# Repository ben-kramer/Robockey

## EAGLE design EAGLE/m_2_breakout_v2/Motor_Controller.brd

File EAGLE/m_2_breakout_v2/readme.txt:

Notes on PCB etching:
1. Make sure you are printing a mirror of the board in EAGLE.
2. print consecutive boards on different parts of the page to save transparencies
	a. Do a test print: put a sharpie mark on the top-side, upper left corner of the page to see which way the printer takes paper
	b. Alternatively, group everything on 1 page first! Prepare singles (pages with just 1
	   design per) and full pages. Print the full page first, and reprint any extras. Make sure
	   singles are in different spots.

issues:
1. M2 needs a jump to ground
2. where does mRF go?

etching method
0. designing
	a. for single-layer boards, design circuit using the bottom layer. Wires are on the sides
	   opposite to the things you are mounting.
1. printing
	a. do a test print to make sure you know what direction the printer prints
	b. from EAGLE, make a pdf (or JPEG?) of the circuit that is BLACK and NOTNOTNOT MIRRORED
		i. look into using JPEGs so multiple pictures can be merged into 1 sheet
	c. take a transparency and mark it with a k or other non-symmetrical letter on the top left
	d. print out the circuits
		i. top and bottom layers
		ii. pad layer
		iii. hole layer
	e. fill in any holes with a fine-tip sharpie
	f. cut out circuits using scissors or xacto. Place circuit on top of board and cut (xacto works nicely for this). Mark anything else (like holes) that is too thin with a sharpie
2. Etching step 1 - photodevelopment
	a. clean transparency first with a duster can and water thorougly.
	b. minimizing fingerprints, wet a lintless towel/cloth with water and gently
	   rub it across the top of the circuit transparency. Make sure to spread the
	   water evenly.
	c. turn off lights, turn on red lights
	d. unpeel protective layer from copper and stick the transparency to the board using the water on the board. Compress the two to ensure they stick together.
	d. Place the board under glass and turn the LED light on for 10 minutes.
	e. Remove board from LED light, turning it off, and place in etching solution. With glove,
	   wiggle board around. This should take no more than 1.5 minutes. If it takes longer, add
	   more positive developer. Towards the end you might have to take one side of the board out
	   and swish around only a fraction of it because the photoresist doesn't develop perfectly
	   evenly.
	f. wash board under cold water
	g. dry board
	h. fill in errors with sharpie
3. Etching step 2 - etching
	a. place board in cupric acid. Ensure cupric acid is a nice green. If it's yellow or brown,
	   add more H202.
	b. swish with the large end of a funnel until board etches.
	c. Note: if etching is still slow after adding H202, add some HCl
	d. rinse board in cold water
	e. rinse board with acetone.
		i. put a little acetone on top of the board, swish it around, and remove it with a sponge.
	f. check for errors
		i. label each error found on the board. Put identifying marks below or to the right of the area, unless doing so is impossible.

todo:

update pinmap

1. add out for breakbeam led
2. add switch bank
3. add bicolor led spot
4. switch motor signal connectors

add enable pins for bridges

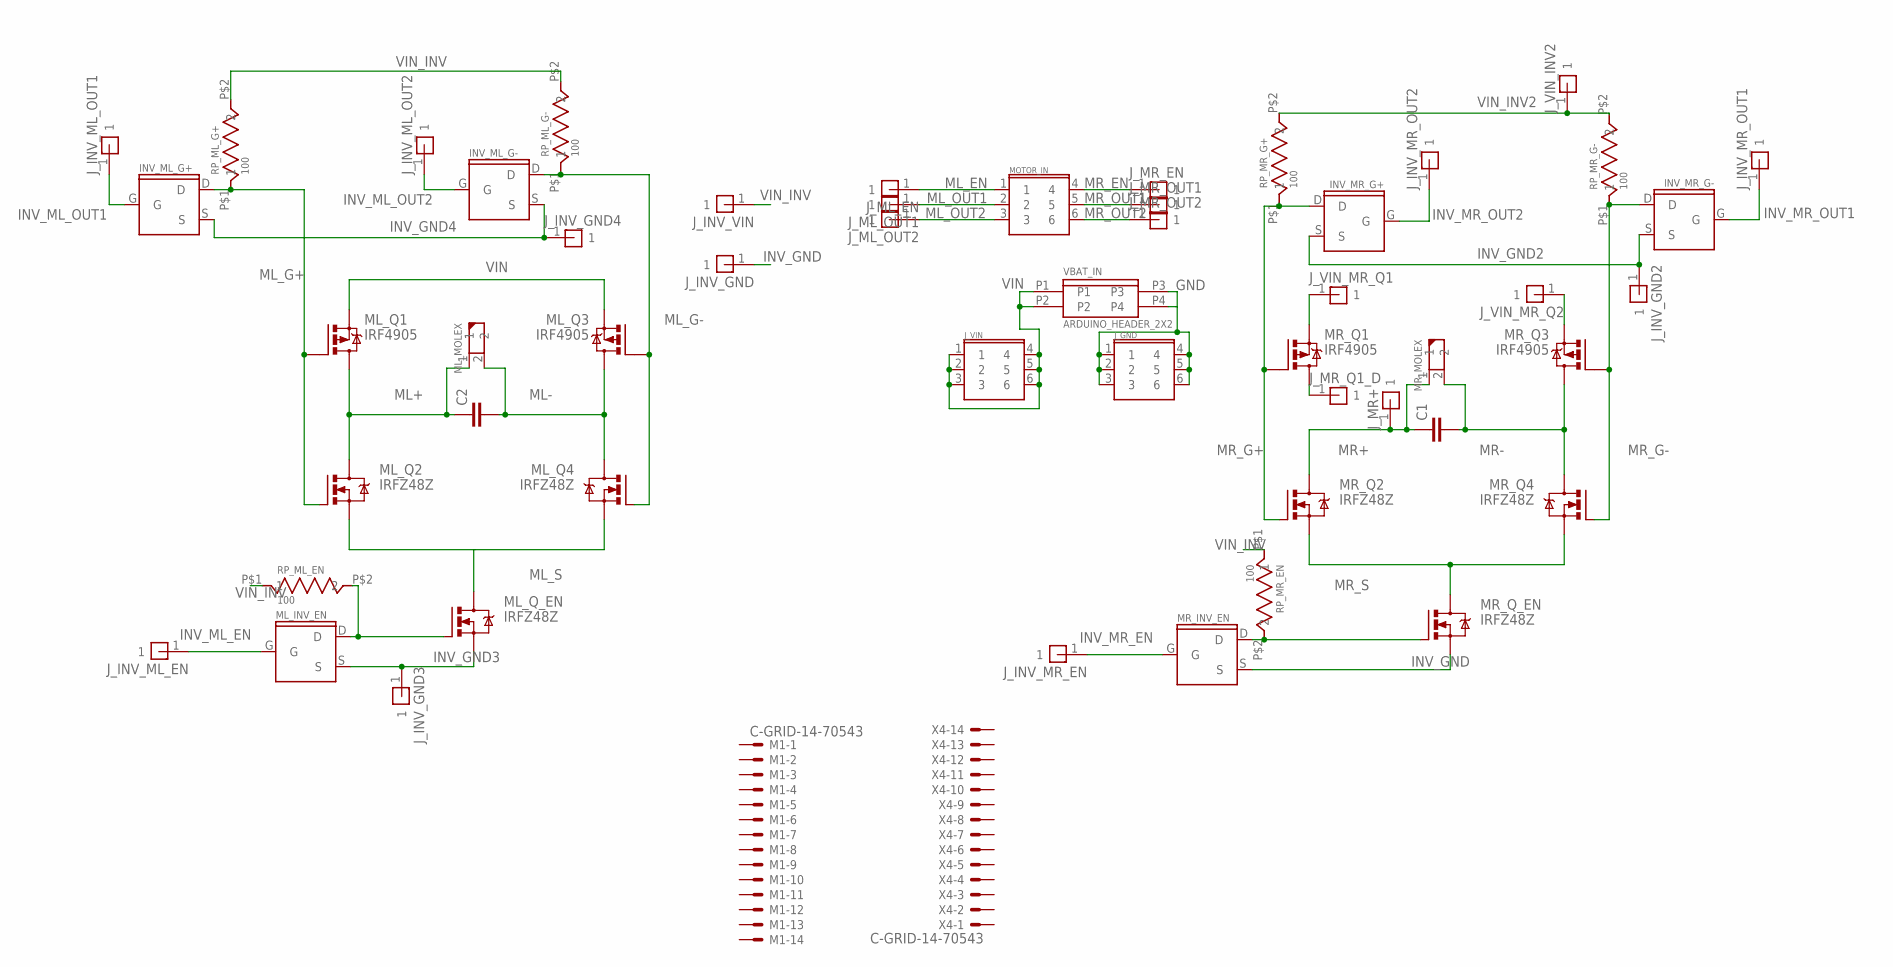
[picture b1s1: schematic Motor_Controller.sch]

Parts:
C1, C2: C5/3; C5B3
INV_ML_G+: 2N7000; TO-92
INV_ML_G-: 2N7000; TO-92
INV_MR_G+: 2N7000; TO-92
INV_MR_G-: 2N7000; TO-92
J_GND: ARDUINO_HEADER_3X2
J_INV_GND, J_INV_GND2, J_INV_GND3, J_INV_GND4: ARDUINO_HEADER_1X1_OCTAGON
J_INV_ML_EN: ARDUINO_HEADER_1X1_OCTAGON
J_INV_ML_OUT1, J_INV_ML_OUT2: ARDUINO_HEADER_1X1_OCTAGON
J_INV_MR_EN: ARDUINO_HEADER_1X1_OCTAGON
J_INV_MR_OUT1, J_INV_MR_OUT2: ARDUINO_HEADER_1X1_OCTAGON
J_INV_VIN: ARDUINO_HEADER_1X1_OCTAGON
J_ML_EN: ARDUINO_HEADER_1X1_OCTAGON
J_ML_OUT1, J_ML_OUT2: ARDUINO_HEADER_1X1_OCTAGON
J_MR+: ARDUINO_HEADER_1X1_OCTAGON
J_MR_EN: ARDUINO_HEADER_1X1_OCTAGON
J_MR_OUT1, J_MR_OUT2: ARDUINO_HEADER_1X1_OCTAGON
J_MR_Q1_D: ARDUINO_HEADER_1X1_OCTAGON
J_VIN: ARDUINO_HEADER_3X2
J_VIN_INV2: ARDUINO_HEADER_1X1_OCTAGON
J_VIN_MR_Q1, J_VIN_MR_Q2: ARDUINO_HEADER_1X1_OCTAGON
M1: C-GRID-14-70543; 70543-14
ML_INV_EN: 2N7000; TO-92
ML_MOLEX: MOLEX_2_PIN
ML_Q1, ML_Q3: IRF4905; TO220BH
ML_Q2, ML_Q4: IRFZ48Z; TO220BH
ML_Q_EN: IRFZ48Z; TO220BH
MOTOR_IN: ARDUINO_HEADER_3X2
MR_INV_EN: 2N7000; TO-92
MR_MOLEX: MOLEX_2_PIN
MR_Q1, MR_Q3: IRF4905; TO220BH
MR_Q2, MR_Q4: IRFZ48Z; TO220BH
MR_Q_EN: IRFZ48Z; TO220BH
RP_ML_EN: 100; RESISTOR_THROUGH_8MM
RP_ML_G+: 100; RESISTOR_THROUGH_8MM
RP_ML_G-: 100; RESISTOR_THROUGH_8MM
RP_MR_EN: 100; RESISTOR_THROUGH_8MM
RP_MR_G+: 100; RESISTOR_THROUGH_8MM
RP_MR_G-: 100; RESISTOR_THROUGH_8MM
VBAT_IN: ARDUINO_HEADER_2X2
X4: C-GRID-14-70543; 70543-14

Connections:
GND: J_GND.1, J_GND.2, J_GND.3, J_GND.4, J_GND.5, J_GND.6, VBAT_IN.P3, VBAT_IN.P4
INV_GND: J_INV_GND.1, MR_INV_EN.S, MR_Q_EN.S
INV_GND2: INV_MR_G+.S, INV_MR_G-.S, J_INV_GND2.1
INV_GND3: J_INV_GND3.1, ML_INV_EN.S, ML_Q_EN.S
INV_GND4: INV_ML_G+.S, INV_ML_G-.S, J_INV_GND4.1
INV_ML_EN: J_INV_ML_EN.1, ML_INV_EN.G
INV_ML_OUT1: INV_ML_G+.G, J_INV_ML_OUT1.1
INV_ML_OUT2: INV_ML_G-.G, J_INV_ML_OUT2.1
INV_MR_EN: J_INV_MR_EN.1, MR_INV_EN.G
INV_MR_OUT1: INV_MR_G-.G, J_INV_MR_OUT1.1
INV_MR_OUT2: INV_MR_G+.G, J_INV_MR_OUT2.1
ML+: C2.1, ML_MOLEX.1, ML_Q1.D, ML_Q2.D
ML-: C2.2, ML_MOLEX.2, ML_Q3.D, ML_Q4.D
ML_EN: J_ML_EN.1, MOTOR_IN.1
ML_G+: INV_ML_G+.D, ML_Q1.G, ML_Q2.G, RP_ML_G+.P$1 (1)
ML_G-: INV_ML_G-.D, ML_Q3.G, ML_Q4.G, RP_ML_G-.P$1 (1)
ML_OUT1: J_ML_OUT1.1, MOTOR_IN.2
ML_OUT2: J_ML_OUT2.1, MOTOR_IN.3
ML_S: ML_Q2.S, ML_Q4.S, ML_Q_EN.D
MR+: C1.1, J_MR+.1, MR_MOLEX.1, MR_Q2.D
MR-: C1.2, MR_MOLEX.2, MR_Q3.D, MR_Q4.D
MR_EN: J_MR_EN.1, MOTOR_IN.4
MR_G+: INV_MR_G+.D, MR_Q1.G, MR_Q2.G, RP_MR_G+.P$1 (1)
MR_G-: INV_MR_G-.D, MR_Q3.G, MR_Q4.G, RP_MR_G-.P$1 (1)
MR_OUT1: J_MR_OUT1.1, MOTOR_IN.5
MR_OUT2: J_MR_OUT2.1, MOTOR_IN.6
MR_Q1_D: J_MR_Q1_D.1, MR_Q1.D
MR_S: MR_Q2.S, MR_Q4.S, MR_Q_EN.D
unnamed: MR_INV_EN.D, MR_Q_EN.G, RP_MR_EN.P$2 (2)
unnamed: ML_INV_EN.D, ML_Q_EN.G, RP_ML_EN.P$2 (2)
unnamed: J_VIN_MR_Q1.1, MR_Q1.S
unnamed: J_VIN_MR_Q2.1, MR_Q3.S
VIN: J_VIN.1, J_VIN.2, J_VIN.3, J_VIN.4, J_VIN.5, J_VIN.6, ML_Q1.S, ML_Q3.S, VBAT_IN.P1, VBAT_IN.P2
VIN_INV: J_INV_VIN.1, RP_ML_EN.P$1 (1), RP_ML_G+.P$2 (2), RP_ML_G-.P$2 (2), RP_MR_EN.P$1 (1)
VIN_INV2: J_VIN_INV2.1, RP_MR_G+.P$2 (2), RP_MR_G-.P$2 (2)

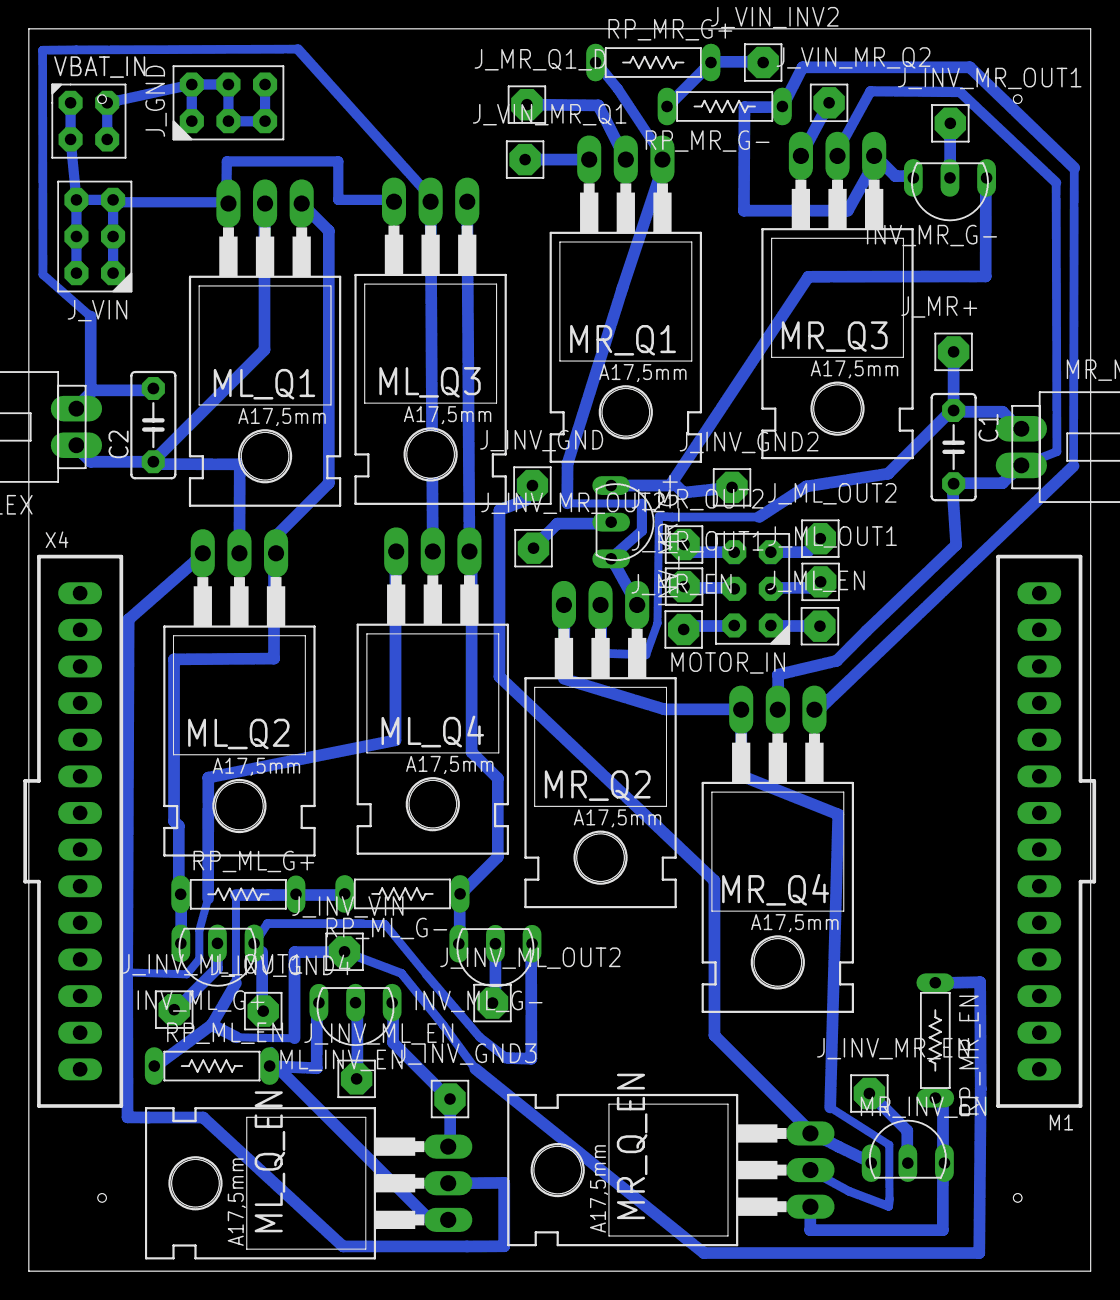
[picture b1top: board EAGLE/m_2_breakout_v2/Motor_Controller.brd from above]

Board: 2 copper layers, 73.6 x 86.2 mm, 54 parts (0 on the bottom side), 35 nets.

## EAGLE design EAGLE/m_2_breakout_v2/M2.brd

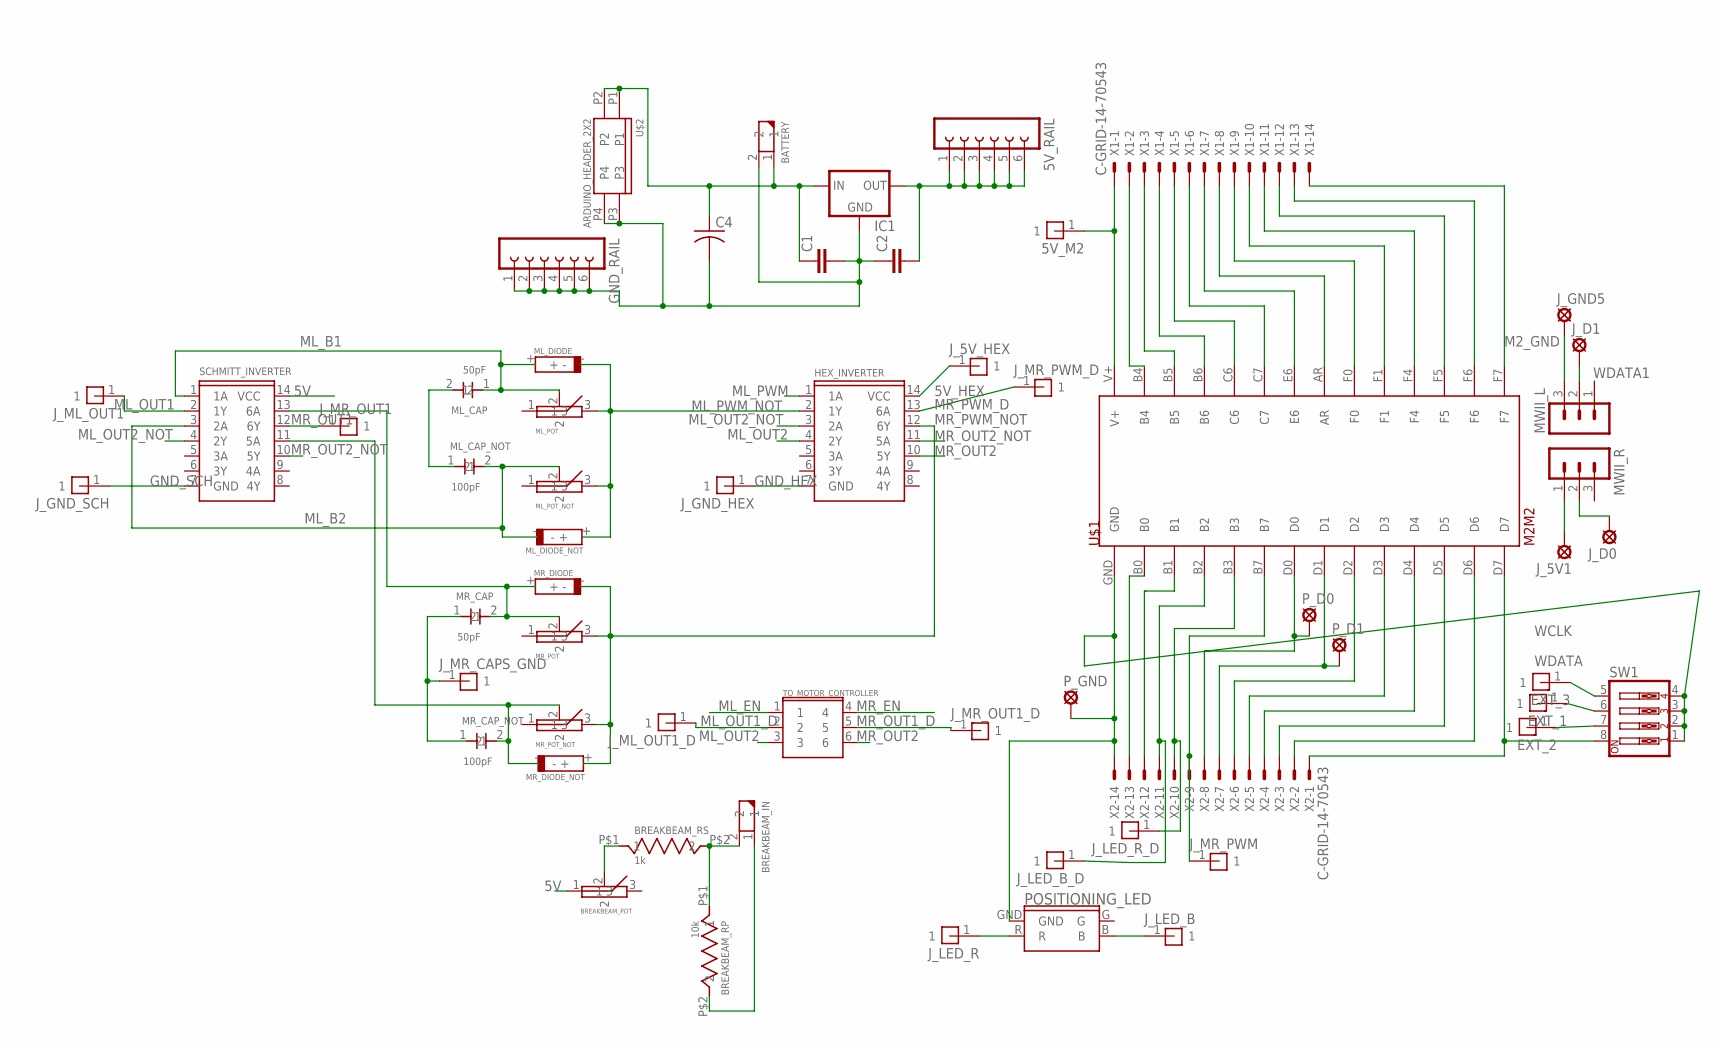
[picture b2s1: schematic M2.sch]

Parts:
5V_M2: ARDUINO_HEADER_1X1_OCTAGON
5V_RAIL: FE06-1; FE06
BATTERY: MOLEX_2_PIN
BREAKBEAM_IN: MOLEX_2_PIN
BREAKBEAM_POT: POTENTIOMETER_1
BREAKBEAM_RP: 10k; RESISTOR_THROUGH_8MM
BREAKBEAM_RS: 1k; RESISTOR_THROUGH_8MM
C1, C2: C2,5-3; C2.5-3
C4: C-US050-025X075; C050-025X075
EXT_1, EXT_2, EXT_3: ARDUINO_HEADER_1X1_OCTAGON
GND_RAIL: FE06-1; FE06
HEX_INVERTER: SN74HC04N_HEX_INVERTER; DIP14
IC1: 78MXXS
J_5V1: LSP10
J_5V_HEX: ARDUINO_HEADER_1X1_OCTAGON
J_D0, J_D1: LSP10
J_GND5: LSP10
J_GND_HEX: ARDUINO_HEADER_1X1_OCTAGON
J_GND_SCH: ARDUINO_HEADER_1X1_OCTAGON
J_LED_B: ARDUINO_HEADER_1X1_OCTAGON
J_LED_B_D: ARDUINO_HEADER_1X1_OCTAGON
J_LED_R: ARDUINO_HEADER_1X1_OCTAGON
J_LED_R_D: ARDUINO_HEADER_1X1_OCTAGON
J_ML_OUT1, J_ML_OUT1_D: ARDUINO_HEADER_1X1_OCTAGON
J_MR_CAPS_GND: ARDUINO_HEADER_1X1_OCTAGON
J_MR_OUT1, J_MR_OUT1_D: ARDUINO_HEADER_1X1_OCTAGON
J_MR_PWM: ARDUINO_HEADER_1X1_OCTAGON
J_MR_PWM_D: ARDUINO_HEADER_1X1_OCTAGON
ML_CAP: 50pF; CERAMIC_CAPACITOR
ML_CAP_NOT: 100pF; CERAMIC_CAPACITOR
ML_DIODE: 1N914B
ML_DIODE_NOT: 1N914B
ML_POT: POTENTIOMETER_1
ML_POT_NOT: POTENTIOMETER_1
MR_CAP: 50pF; CERAMIC_CAPACITOR
MR_CAP_NOT: 100pF; CERAMIC_CAPACITOR
MR_DIODE: 1N914B
MR_DIODE_NOT: 1N914B
MR_POT: POTENTIOMETER_1
MR_POT_NOT: POTENTIOMETER_1
MWII_L: MA03-1
MWII_R: MA03-1
POSITIONING_LED: RGB_LED; RBG_LED
P_D0, P_D1: LSP10
P_GND: LSP10
SCHMITT_INVERTER: SN74HC14N_SCHMITT_INVERTER; DIP14
SW1: SW_DIP-4; EDG-04
TO_MOTOR_CONTROLLER: ARDUINO_HEADER_3X2
U$1: M2M2; M2
U$2: ARDUINO_HEADER_2X2
X1, X2: C-GRID-14-70543; 70543-14

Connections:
5V: 5V_RAIL.1, 5V_RAIL.2, 5V_RAIL.3, 5V_RAIL.4, 5V_RAIL.5, 5V_RAIL.6, BREAKBEAM_POT.1, C2.2, IC1.OUT, SCHMITT_INVERTER.14 (VCC)
5V_1: J_5V1.MP, MWII_R.1
5V_HEX: HEX_INVERTER.14 (VCC), J_5V_HEX.1
B2: J_LED_B_D.1, U$1.B2, X2.11
B3: J_LED_R_D.1, U$1.B3, X2.10
B5: U$1.B5, X1.3
BREAKBEAM_OUT: BREAKBEAM_IN.2, BREAKBEAM_RP.P$1 (1), BREAKBEAM_RS.P$2 (2), U$1.C6, X1.5
C7: U$1.C7, X1.6
GND: ML_CAP.2, ML_CAP_NOT.1
GND_HEX: HEX_INVERTER.7 (GND), J_GND_HEX.1
GND_SCH: J_GND_SCH.1, SCHMITT_INVERTER.7 (GND)
IN_GND: BATTERY.2, C1.2, C2.1, C4.2, GND_RAIL.1, GND_RAIL.2, GND_RAIL.3, GND_RAIL.4, GND_RAIL.5, GND_RAIL.6, IC1.GND, U$2.P3, U$2.P4
LED_B: J_LED_B.1, POSITIONING_LED.B
LED_R: J_LED_R.1, POSITIONING_LED.R
M2_GND: BREAKBEAM_IN.1, BREAKBEAM_RP.P$2 (2), J_GND5.MP, MWII_L.3
ML_B1: ML_CAP.1, ML_DIODE.+, ML_POT.2, SCHMITT_INVERTER.1 (1A)
ML_B2: ML_CAP_NOT.2, ML_DIODE_NOT.-, ML_POT_NOT.2, SCHMITT_INVERTER.3 (2A)
ML_EN: TO_MOTOR_CONTROLLER.1, U$1.B0, X2.13
ML_OUT1: J_ML_OUT1.1, SCHMITT_INVERTER.2 (1Y)
ML_OUT1_D: J_ML_OUT1_D.1, TO_MOTOR_CONTROLLER.2
ML_OUT2: HEX_INVERTER.4 (2Y), TO_MOTOR_CONTROLLER.3
ML_OUT2_NOT: HEX_INVERTER.3 (2A), SCHMITT_INVERTER.4 (2Y)
ML_PWM: HEX_INVERTER.1 (1A), U$1.B6, X1.4
ML_PWM_NOT: HEX_INVERTER.2 (1Y), ML_DIODE.-, ML_DIODE_NOT.+, ML_POT.3, ML_POT_NOT.3
MR_CAPS_GND: J_MR_CAPS_GND.1, MR_CAP.1, MR_CAP_NOT.1
MR_EN: TO_MOTOR_CONTROLLER.4, U$1.B1, X2.12
MR_OUT1: J_MR_OUT1.1, SCHMITT_INVERTER.12 (6Y)
MR_OUT1_D: J_MR_OUT1_D.1, TO_MOTOR_CONTROLLER.5
MR_OUT2: HEX_INVERTER.10 (5Y), TO_MOTOR_CONTROLLER.6
MR_OUT2_NOT: HEX_INVERTER.11 (5A), SCHMITT_INVERTER.10 (5Y)
MR_PWM: J_MR_PWM.1, U$1.B7, X2.9
MR_PWM_D: HEX_INVERTER.13 (6A), J_MR_PWM_D.1
MR_PWM_NOT: HEX_INVERTER.12 (6Y), MR_DIODE.-, MR_DIODE_NOT.+, MR_POT.3, MR_POT_NOT.3
unnamed: MR_CAP.2, MR_DIODE.+, MR_POT.2, SCHMITT_INVERTER.13 (6A)
unnamed: U$1.B4, X1.2
unnamed: POSITIONING_LED.GND, P_GND.MP, SW1.1, SW1.2, SW1.3, SW1.4, U$1.GND, X2.14
unnamed: MR_CAP_NOT.2, MR_DIODE_NOT.-, MR_POT_NOT.2, SCHMITT_INVERTER.11 (5A)
unnamed: EXT_2.1, SW1.7
unnamed: BREAKBEAM_POT.2, BREAKBEAM_RS.P$1 (1)
unnamed: U$1.E6, X1.7
unnamed: U$1.AR, X1.8
unnamed: U$1.F0, X1.9
unnamed: U$1.F1, X1.10
unnamed: U$1.F4, X1.11
unnamed: U$1.F5, X1.12
unnamed: U$1.F6, X1.13
unnamed: EXT_1.1, SW1.6
unnamed: U$1.F7, X1.14
unnamed: EXT_3.1, SW1.5
unnamed: 5V_M2.1, U$1.V+, X1.1
unnamed: U$1.D2, X2.6
unnamed: U$1.D3, X2.5
unnamed: U$1.D4, X2.4
unnamed: U$1.D5, X2.3
unnamed: U$1.D6, X2.2
unnamed: SW1.8, U$1.D7, X2.1
VIN: BATTERY.1, C1.1, C4.1, IC1.IN, U$2.P1, U$2.P2
WCLK: P_D0.MP, U$1.D0, X2.8
WCLK_1: J_D0.MP, MWII_R.2
WDATA: P_D1.MP, U$1.D1, X2.7
WDATA1: J_D1.MP, MWII_L.2

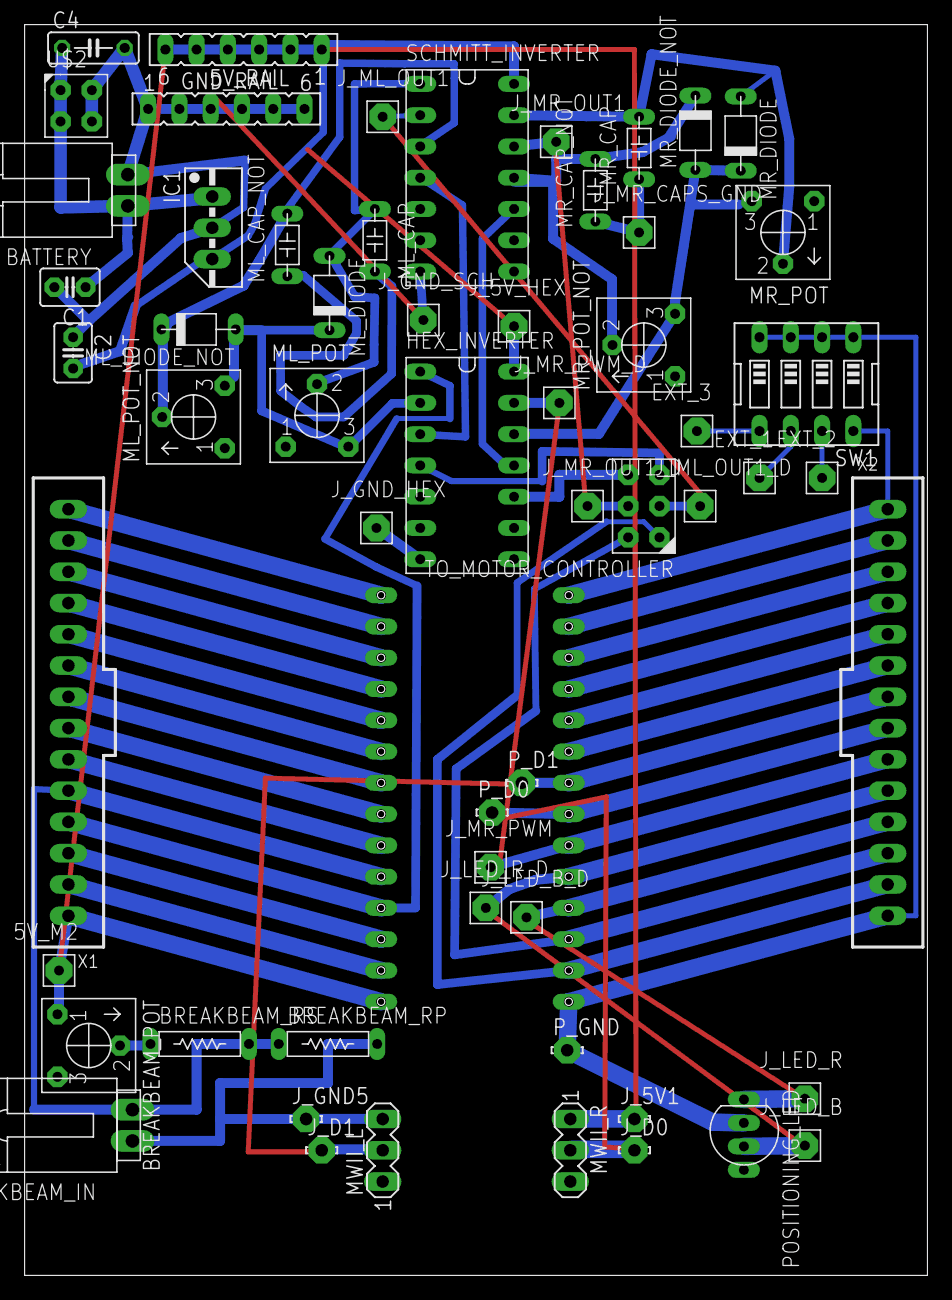
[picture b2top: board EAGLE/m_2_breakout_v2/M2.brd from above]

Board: 2 copper layers, 73.3 x 101.6 mm, 59 parts (0 on the bottom side), 61 nets.

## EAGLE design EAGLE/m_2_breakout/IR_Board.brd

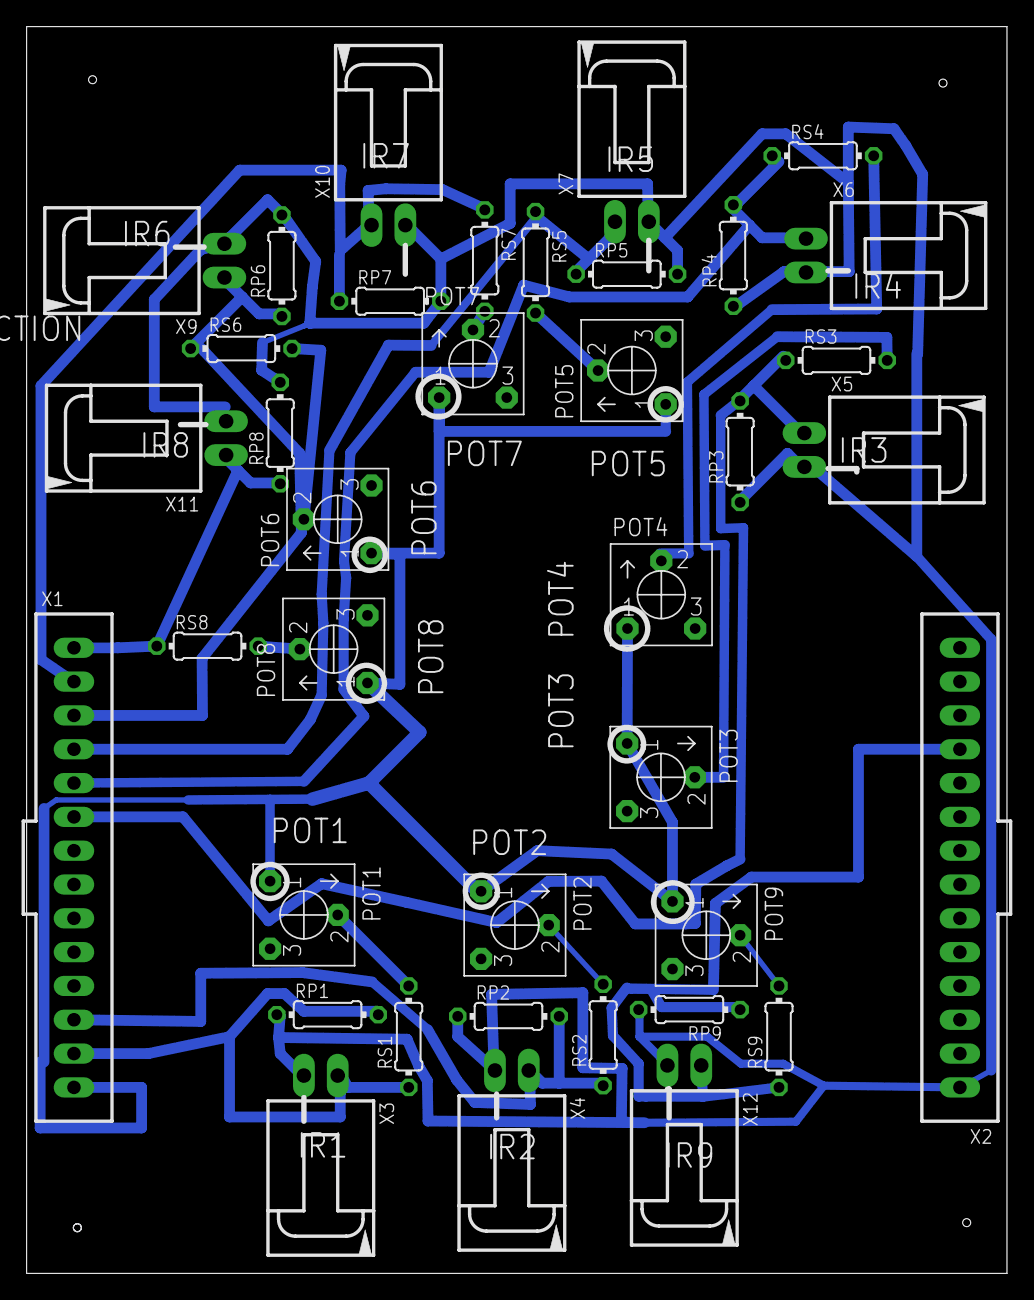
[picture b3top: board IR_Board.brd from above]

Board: 2 copper layers, 73.6 x 93.7 mm, 38 parts (0 on the bottom side), 20 nets.

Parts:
POT1, POT2, POT3, POT4, POT5, POT6, POT7, POT8, POT9: POTENTIOMETER_1
RP1, RP2, RP3, RP4, RP5, RP6, RP7, RP8, RP9: 0204/7
RS1, RS2, RS3, RS4, RS5, RS6, RS7, RS8, RS9: 0204/7
X1, X2: C-GRID-14-70543; 70543-14
X3, X4, X5, X6, X7, X9, X10, X11, X12: C-GRID-02-70553; 70553-02

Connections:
5V: POT1.1, POT2.1, POT3.1, POT4.1, POT5.1, POT6.1, POT7.1, POT8.1, POT9.1, X1.14
GND: RP1.1, RP2.1, RP3.1, RP4.1, RP5.2, RP6.2, RP7.2, RP8.2, RP9.2, X2.1, X3.2, X4.2, X5.2, X6.2, X7.2, X9.2, X10.2, X11.2, X12.2
IR1: RP1.2, RS1.1, X1.13, X3.1
IR2: RP2.2, RS2.1, X1.12, X4.1
IR3: RP3.2, RS3.1, X1.6, X5.1
IR4: RP4.2, RS4.1, X1.5, X6.1
IR5: RP5.1, RS5.1, X1.4, X7.1
IR6: RP6.1, RS6.1, X1.3, X9.1
IR7: RP7.1, RS7.1, X1.2, X10.1
IR8: RP8.1, RS8.1, X1.1, X11.1
IR9: RP9.1, RS9.1, X2.11, X12.1
unnamed: POT1.2, RS1.2
unnamed: POT3.2, RS3.2
unnamed: POT2.2, RS2.2
unnamed: POT5.2, RS5.2
unnamed: POT6.2, RS6.2
unnamed: POT7.2, RS7.2
unnamed: POT9.2, RS9.2
unnamed: POT8.2, RS8.2
unnamed: POT4.2, RS4.2

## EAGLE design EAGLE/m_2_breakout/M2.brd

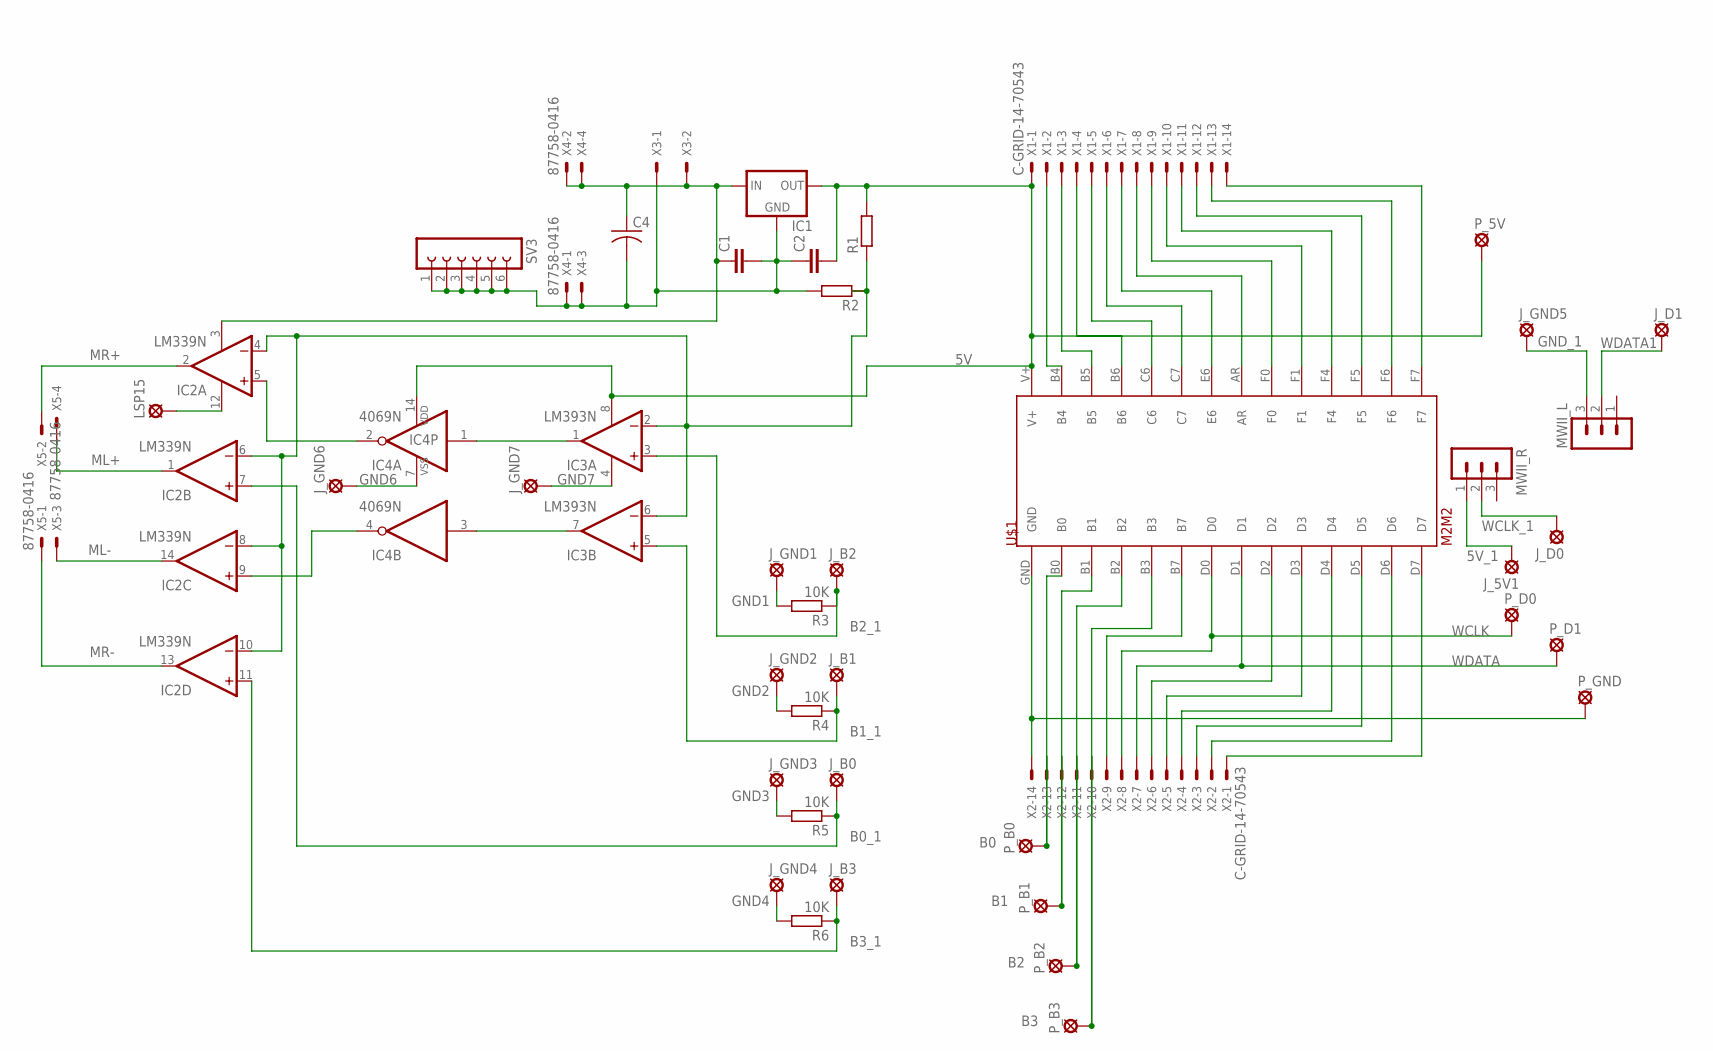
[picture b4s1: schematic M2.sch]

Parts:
C1, C2: C2,5-3; C2.5-3
C4: C-US050-025X075; C050-025X075
IC1: 78MXXS
IC2: LM339N; DIL14
IC3: LM393N; DIL08
IC4: 4069N; DIL14
J_5V1: LSP10
J_B0, J_B1, J_B2, J_B3: LSP10
J_D0, J_D1: LSP10
J_GND1, J_GND2, J_GND3, J_GND4, J_GND5, J_GND6, J_GND7: LSP10
LSP15: LSP10
MWII_L: MA03-1
MWII_R: MA03-1
P_5V: LSP10
P_B0, P_B1, P_B2, P_B3: LSP10
P_D0, P_D1: LSP10
P_GND: LSP10
R1, R2: R-EU_0204/7; 0204/7
R3, R4, R5, R6: 10K; 0204/7
SV3: FE06-1; FE06
U$1: M2M2; M2
X1, X2: C-GRID-14-70543; 70543-14
X3: KK-156-2
X4, X5: 87758-0416

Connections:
5V: C2.2, IC1.OUT, IC3.8 (V+), IC4.14 (VDD), P_5V.MP, R1.2, U$1.V+, X1.1
5V_1: J_5V1.MP, MWII_R.1
B0: P_B0.MP, U$1.B0, X2.13
B0_1: IC2.7 (+IN), J_B0.MP, R5.1
B1: P_B1.MP, U$1.B1, X2.12
B1_1: IC3.5 (+IN), J_B1.MP, R4.1
B2: P_B2.MP, U$1.B2, X2.11
B2_1: IC3.3 (+IN), J_B2.MP, R3.1
B3: P_B3.MP, U$1.B3, X2.10
B3_1: IC2.11 (+IN), J_B3.MP, R6.1
GND1: J_GND1.MP, R3.2
GND2: J_GND2.MP, R4.2
GND3: J_GND3.MP, R5.2
GND4: J_GND4.MP, R6.2
GND6: IC4.7 (VSS), J_GND6.MP
GND7: IC3.4 (V-), J_GND7.MP
GND_1: J_GND5.MP, MWII_L.3
ML+: IC2.1 (OUT), X5.4
ML-: IC2.14 (OUT), X5.3
MR+: IC2.2 (OUT), X5.2
MR-: IC2.13 (OUT), X5.1
unnamed: U$1.B4, X1.2
unnamed: U$1.B5, X1.3
unnamed: U$1.B6, X1.4
unnamed: U$1.C6, X1.5
unnamed: U$1.C7, X1.6
unnamed: U$1.E6, X1.7
unnamed: U$1.AR, X1.8
unnamed: U$1.F0, X1.9
unnamed: U$1.F1, X1.10
unnamed: U$1.F4, X1.11
unnamed: U$1.F5, X1.12
unnamed: U$1.F6, X1.13
unnamed: U$1.F7, X1.14
unnamed: IC2.4 (-IN), IC2.6 (-IN), IC2.8 (-IN), IC2.10 (-IN), IC3.2 (-IN), IC3.6 (-IN), R1.1, R2.1
unnamed: P_GND.MP, U$1.GND, X2.14
unnamed: U$1.B7, X2.9
unnamed: U$1.D2, X2.6
unnamed: U$1.D3, X2.5
unnamed: U$1.D4, X2.4
unnamed: U$1.D5, X2.3
unnamed: U$1.D6, X2.2
unnamed: U$1.D7, X2.1
unnamed: IC3.1 (OUT), IC4.1 (I)
unnamed: IC3.7 (OUT), IC4.3 (I)
unnamed: IC2.5 (+IN), IC4.2 (O)
unnamed: C1.1, C4.1, IC1.IN, IC2.3 (V+), X3.2, X4.2, X4.4
unnamed: IC2.9 (+IN), IC4.4 (O)
unnamed: IC2.12 (GND), LSP15.MP
unnamed: C1.2, C2.1, C4.2, IC1.GND, R2.2, SV3.1, SV3.2, SV3.3, SV3.4, SV3.5, SV3.6, X3.1, X4.1, X4.3
WCLK: P_D0.MP, U$1.D0, X2.8
WCLK_1: J_D0.MP, MWII_R.2
WDATA: P_D1.MP, U$1.D1, X2.7
WDATA1: J_D1.MP, MWII_L.2

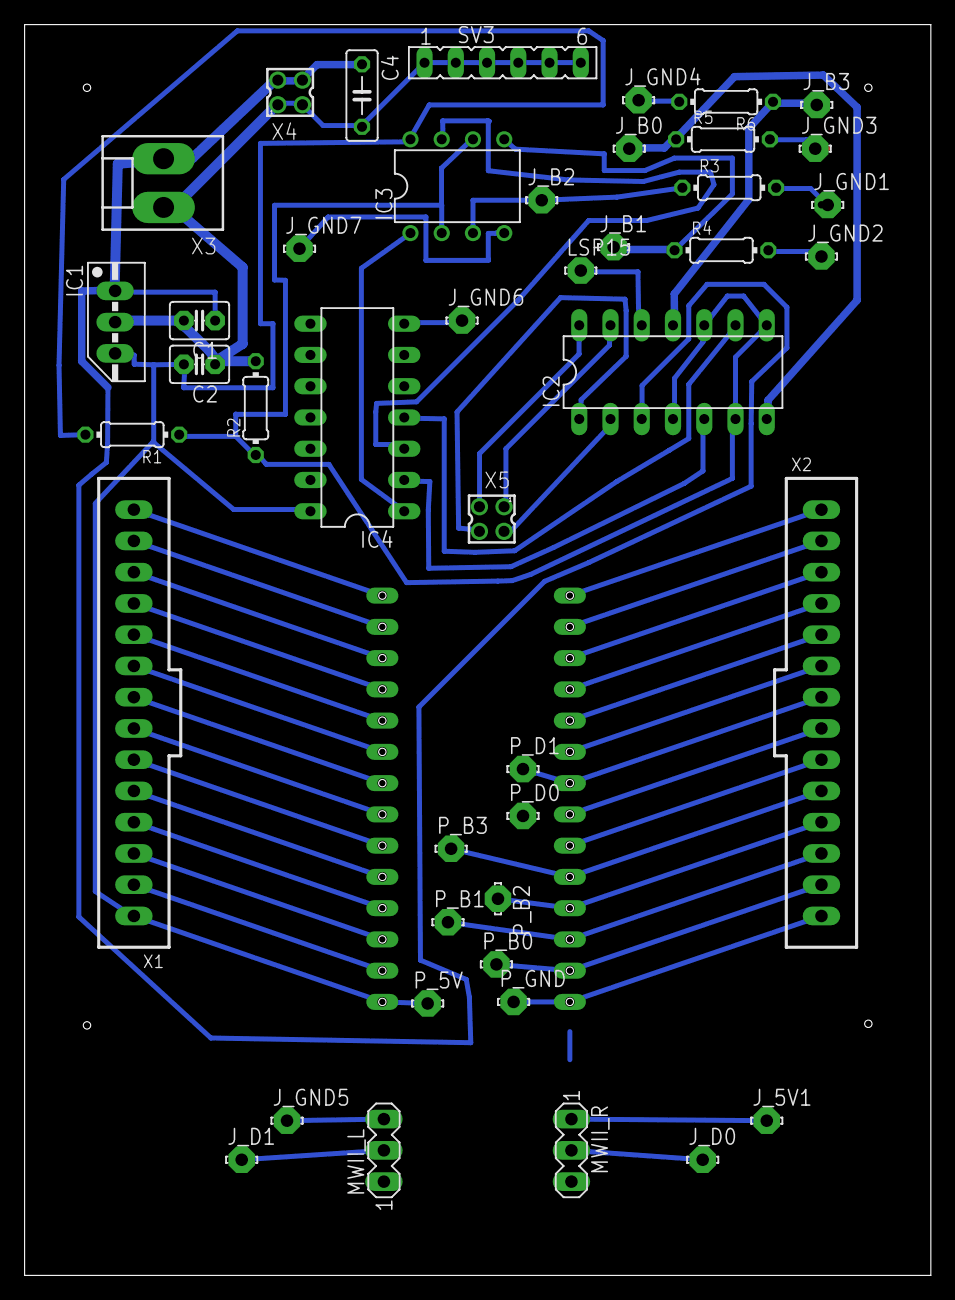
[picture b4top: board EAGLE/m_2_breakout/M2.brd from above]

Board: 2 copper layers, 73.6 x 101.7 mm, 45 parts (0 on the bottom side), 54 nets.

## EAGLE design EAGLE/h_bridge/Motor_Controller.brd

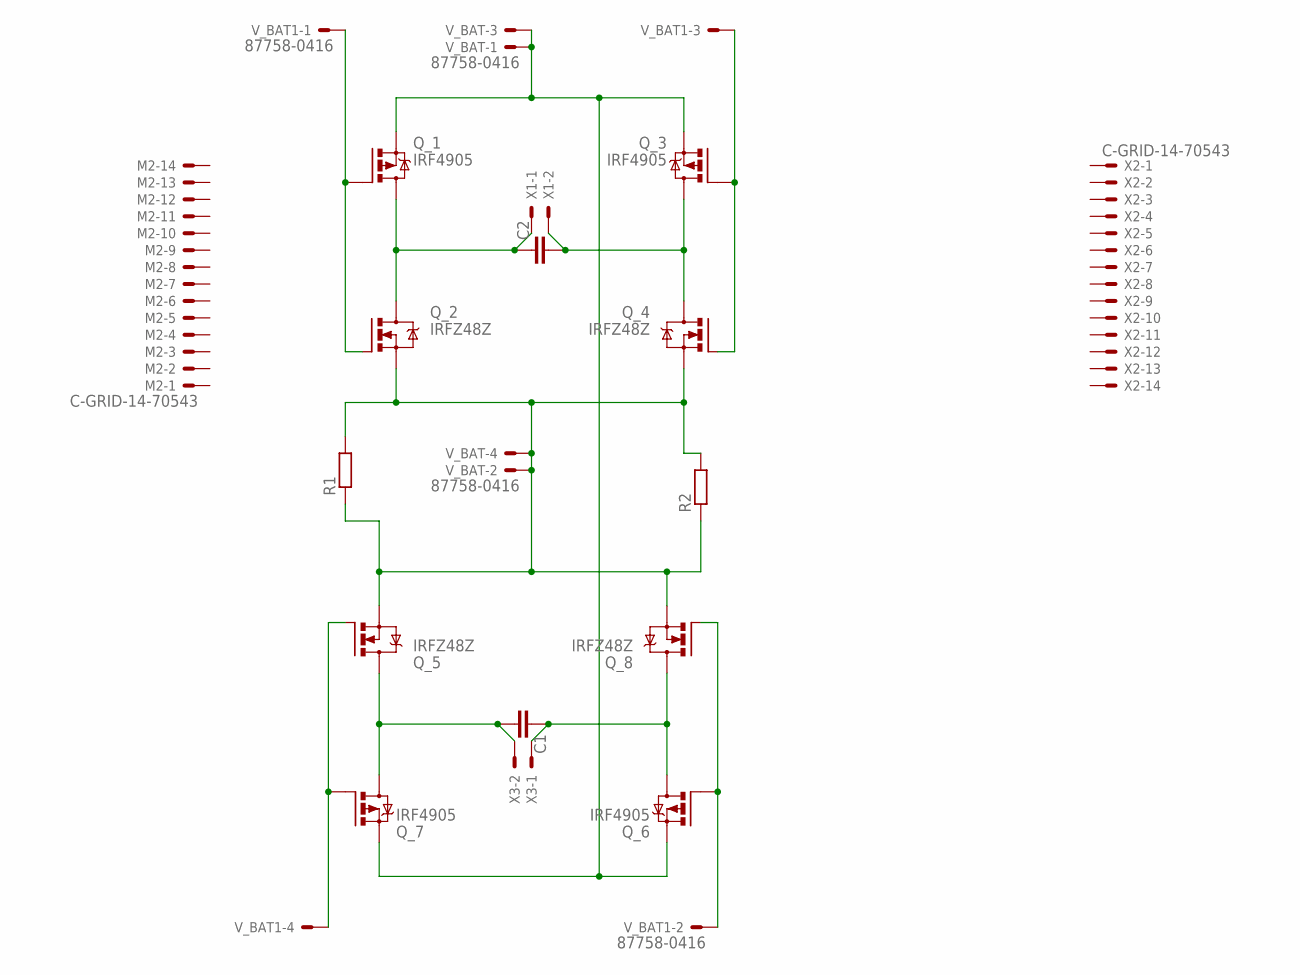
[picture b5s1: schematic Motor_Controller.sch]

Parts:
C1, C2: C5/3; C5B3
M2: C-GRID-14-70543; 70543-14
Q_1, Q_3, Q_6, Q_7: IRF4905; TO220BH
Q_2, Q_4, Q_5, Q_8: IRFZ48Z; TO220BH
R1, R2: R0204/7; 0204/7
V_BAT, V_BAT1: 87758-0416
X1, X3: KK-156-2
X2: C-GRID-14-70543; 70543-14

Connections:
unnamed: C1.2, Q_5.D, Q_7.D, X3.2
unnamed: C2.2, Q_3.D, Q_4.D, X1.2
unnamed: Q_5.G, Q_7.G, V_BAT1.4
unnamed: Q_6.G, Q_8.G, V_BAT1.2
unnamed: Q_2.S, Q_4.S, Q_5.S, Q_8.S, R1.1, R1.2, R2.1, R2.2, V_BAT.2, V_BAT.4
unnamed: Q_3.G, Q_4.G, V_BAT1.3
unnamed: Q_1.G, Q_2.G, V_BAT1.1
Q_1: C1.1, Q_6.D, Q_8.D, X3.1
Q_2: C2.1, Q_1.D, Q_2.D, X1.1
Q_4: Q_1.S, Q_3.S, Q_6.S, Q_7.S, V_BAT.1, V_BAT.3

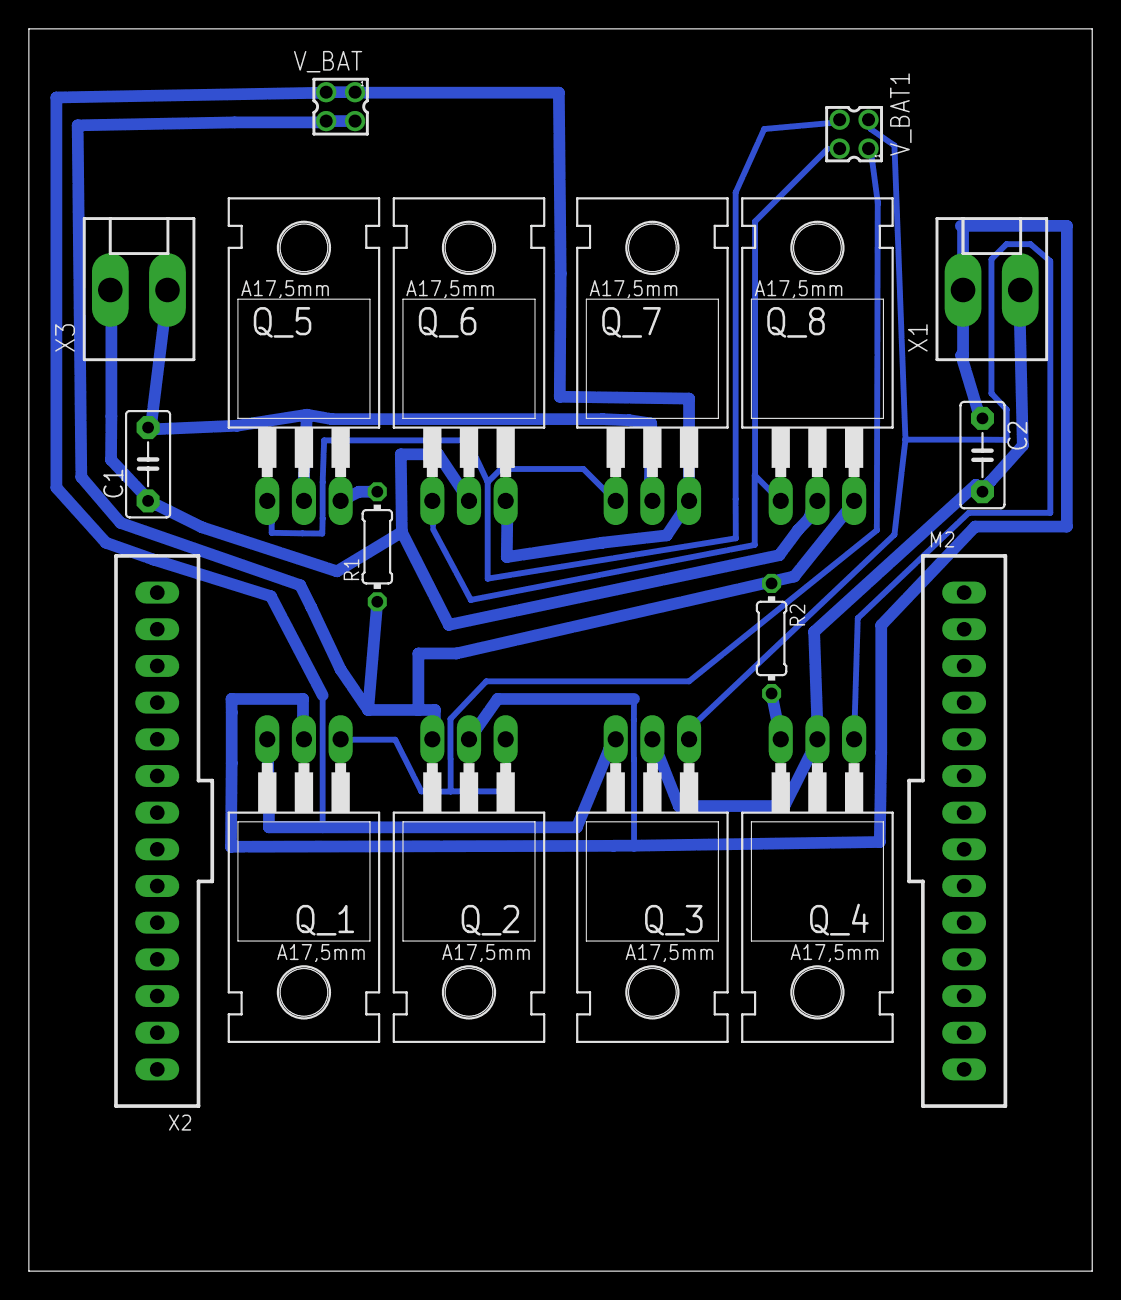
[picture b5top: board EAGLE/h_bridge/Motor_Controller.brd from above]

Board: 2 copper layers, 73.6 x 86.0 mm, 18 parts (0 on the bottom side), 10 nets.
